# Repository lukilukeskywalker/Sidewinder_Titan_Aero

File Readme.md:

# Sidewinder x1 X axis Gantry and Board

The sidewinder x1 is a great printer but, lacking in some aspects of the X axis.
I have tryed to give the printer a better Head, building an original Titan Aero on the x axis, replacing the x board trying to remove the problems the ribbon cable gave to the printer

I have mounted the Head on the X axis gantry, but I haven't been able to test it, so I can only give you some 3d renderings

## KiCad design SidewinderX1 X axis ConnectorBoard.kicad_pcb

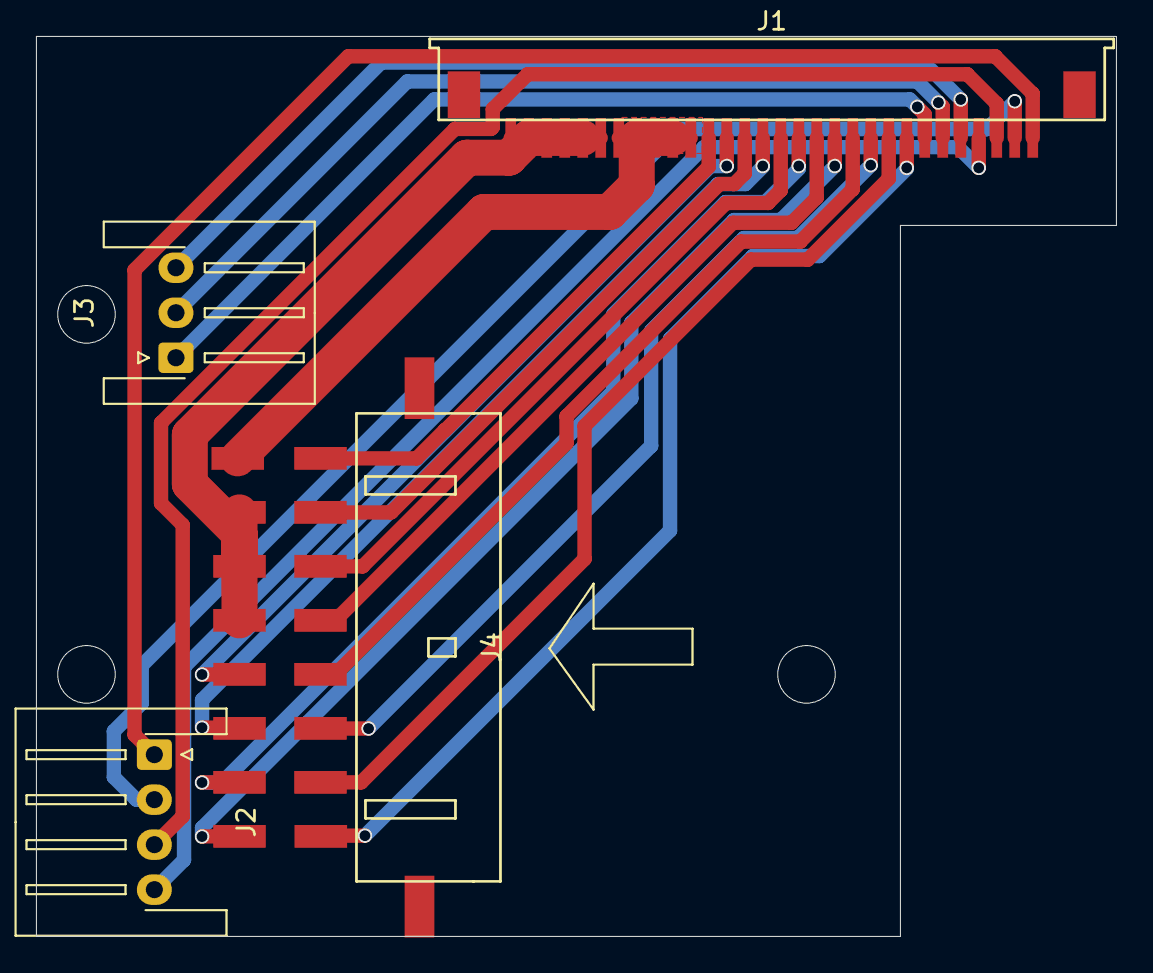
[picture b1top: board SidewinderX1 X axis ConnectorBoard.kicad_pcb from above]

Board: 2 copper layers, 60.0 x 50.0 mm, 4 parts (0 on the bottom side), 21 nets.

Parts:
J1: Sidewinder_30PIN conn; WürthFPC30pins1mm68613014122
J2: X_AXIS_Motor; JST_XH_S4B-XH-A-1_1x04_P2.50mm_Horizontal
J3: Inductiver_Sensor; JST_XH_S3B-XH-A-1_1x03_P2.50mm_Horizontal
J4: Micro MATE-N-LOK 2x8; MicroMATE-N-LOK2x8pins4-794627-6

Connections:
+FAN1: J1.25, J1.26, J1.27, J1.28, J1.29, J1.30, J4.10, J4.11, J4.12
ExtruderMotor_A: J1.8, J4.1
ExtruderMotor_B: J1.9, J4.2
ExtruderMotor_C: J1.10, J4.3
ExtruderMotor_D: J1.11, J4.4
GND: J1.20, J1.21, J1.22, J1.23, J1.24, J4.9
Inductiver_Sensor_Braun: J1.5, J3.3
Inductiver_Sensor_blau: J1.7, J3.1
Inductiver_Sensor_schwarz: J1.6, J3.2
Suzatz_-: J1.12, J4.16
Suzatz_-FAN1: J1.13, J4.5
Suzatz_-FAN2: J1.19, J4.8
Suzatz_B: J1.18, J4.13
Suzatz_G: J1.16, J4.14
Suzatz_R: J1.14, J4.15
Thermistor_1: J1.15, J4.6
Thermistor_2: J1.17, J4.7
X_AXIS_Motor_A: J1.1, J2.1
X_AXIS_Motor_B: J1.2, J2.2
X_AXIS_Motor_C: J1.3, J2.3
X_AXIS_Motor_D: J1.4, J2.4

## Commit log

2022-12-23 [Schematic][Board][3DModel] First Commit
2023-01-03 [Readme]
